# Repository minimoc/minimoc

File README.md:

# miniMoc

**Routeur MIDI hybride DAWless, fait main.**

🇬🇧 In English — miniMoc is a handmade, open-hardware DAWless MIDI router built around a Teensy 4.1: 5 MIDI inputs, 9 outputs, TRS TYPE A + USB Host, a 128x64 OLED screen and a rotary encoder. Route MIDI between your synths and machines with no computer. Its signature feature, Smart Mirror: plug in a PC and the miniMoc's physical ports reappear as identical virtual ports in your DAW — no setup, no drivers. Unplug and you're back to standalone mode. The project is at v0.5.2 (routing, Smart Mirror, MIDI clock sync, Flux transforms — transpose/harmonize/chord progressions —, MIDI generators — LFO/Euclidean/drum patterns — and SD presets are solid; continuous MIDI auto-recording to SD is postponed to a future version). Documentation is currently in French — English translation contributions are very welcome (see CONTRIBUTING.md). Licence: source-available, non-commercial (PolyForm NC for firmware, CC BY-NC for hardware) — personal use is free, commercial use requires permission.

Le miniMoc est un boîtier portable qui route le MIDI entre vos synthés, séquenceurs
et machines — sans ordinateur. cinq entrées (2 TRS Type A + 3 USB), neuf sorties (6 TRS TYPE A + 3 USB), USB Host, un écran OLED 128x64 pixels
et un encodeur pour tout piloter à la main.

> **Smart Mirror** — branchez un PC/MAC/LINUX/SMARTPHONE et les ports physiques du miniMoc réapparaissent
> à l'identique en ports virtuels dans votre DAW. Aucune configuration, aucun pilote
> à installer. Vous débranchez, vous repartez en mode autonome.

---

## Démonstrations vidéo

- **Le projet et l'appel aux compagnons** : https://www.youtube.com/watch?v=sc03914Uq1w
- **Présentation du hardware** (ce que vous recevez, comment c'est fait) : https://youtu.be/FKErdNdDdWI
- **La navigation dans les menus** : https://youtu.be/ahOwxcXlfOY
- **Le smartmirror expliqué** : https://youtu.be/d6lrl4uF-Bw

---

## État du projet — v0.5.2

Le miniMoc en est à sa version 0.5.2, assemblée à la main.

**Ce qui fonctionne et est éprouvé :**
- Routage MIDI complet (mode BASIC par matrice, mode FLUX avancé avec filtrage et
  remapping de canal)
- Smart Mirror (miroir des ports physiques vers le DAW)
- Synchronisation MIDI Clock (horloge interne réglable ou source externe) + écran TRANSPORT
- Transformateurs de Flux : transposition, harmonisation, réharmonisation sur une
  progression d'accords
- Générateurs MIDI internes : LFO, séquenceur euclidien, motifs de batterie pré-enregistrés
- Sauvegarde / rappel des configurations sur carte SD (32 presets utilisateur + 8 d'usine)
- Interface écran OLED + encodeur
- Mise à jour du firmware par OTA depuis l'éditeur web

**Reporté après la V1 :**
- Auto-enregistrement MIDI continu sur carte SD (capture automatique des jams). Le moteur
  existe dans le code mais reste désactivé par défaut : pas de commande pour démarrer/
  arrêter un enregistrement à la volée, pas de fermeture propre du fichier en cours
  d'usage. Sera retravaillé pour une version ultérieure — vos retours d'usage sur ce
  point précis restent les bienvenus.

---

## Ce que c'est (et ce que ce n'est pas)

Le miniMoc est un projet dans un esprit maker. Ce n'est pas un
produit fini sous coque fermée : il se présente sous forme de carte (PCB) avec son
Teensy 4.1, et un *bezel* maintient l'écran en position. Des premiers fichiers 3D de
boîtier et de socle existent (dossiers [`boitier/`](boitier/) et [`socle/`](socle/))
mais restent perfectibles — c'est un terrain de contribution ouvert pour qui aime la CAO.

---

## Matériel

- **Microcontrôleur** : Teensy 4.1 (PJRC)
- **Affichage** : écran OLED monochrome (I²C)
- **Entrées / sorties** : 2+3 IN MIDI, 6+3 OUT MIDI
- **Contrôle** : encodeur rotatif + bouton

Les fichiers de conception (schémas, PCB, BOM) se trouvent dans le dossier
[`hardware/`](hardware/). Le *bezel* à imprimer est dans [`bezel/`](bezel/).

---

## Firmware

Le code du firmware est dans [`firmware/`](firmware/). Il se compile avec
**l'IDE Arduino + Teensyduino**, pour Teensy 4.1.

### Dépendances

Ces bibliothèques **ne sont pas incluses dans ce dépôt**. Installez-les via le
gestionnaire de bibliothèques de l'IDE Arduino (ou elles sont fournies avec
Teensyduino) :

- U8g2
- Arduino MIDI Library (version 5+)
- USBHost_t36 *(fournie avec Teensyduino)*
- MTP_Teensy
- SdFat
- Encoder *(fournie avec Teensyduino)*
- Bounce2

> ⚠️ N'essayez pas de récupérer ces bibliothèques depuis ce dépôt : elles n'y sont
> volontairement pas. Passez par le gestionnaire de bibliothèques Arduino.

Les licences de ces dépendances sont détaillées dans
[`THIRD_PARTY_LICENSES.md`](THIRD_PARTY_LICENSES.md).

---

## Licence

**Sources ouvertes — usage personnel libre, commercialisation sur accord.**

- **Firmware** (dossier `firmware/`) : licence **PolyForm Noncommercial 1.0.0**.
  Vous pouvez l'utiliser, l'étudier, le modifier et le partager **pour un usage
  non commercial**.
- **Matériel** (dossiers `hardware/` et `bezel/`) : licence
  **Creative Commons Attribution-NonCommercial 4.0 (CC BY-NC 4.0)**.

Toute **utilisation commerciale** (vente, intégration dans un produit vendu, etc.)
nécessite mon accord préalable. Si vous souhaitez commercialiser quelque chose à
partir du miniMoc, contactez-moi : c'est tout à fait possible de s'entendre.

Voir les fichiers [`LICENSE`](LICENSE) (firmware) et
[`hardware/LICENSE`](hardware/LICENSE) (matériel).

---

## Contribuer

Le miniMoc avance avec celles et ceux qui l'utilisent. Retours d'usage,
corrections, idées de fonctionnalités, conception d'un boîtier complet : tout est
bienvenu. Voir [`CONTRIBUTING.md`](CONTRIBUTING.md).

---

*miniMoc — conçu et assemblé à la main par François Jacob.*

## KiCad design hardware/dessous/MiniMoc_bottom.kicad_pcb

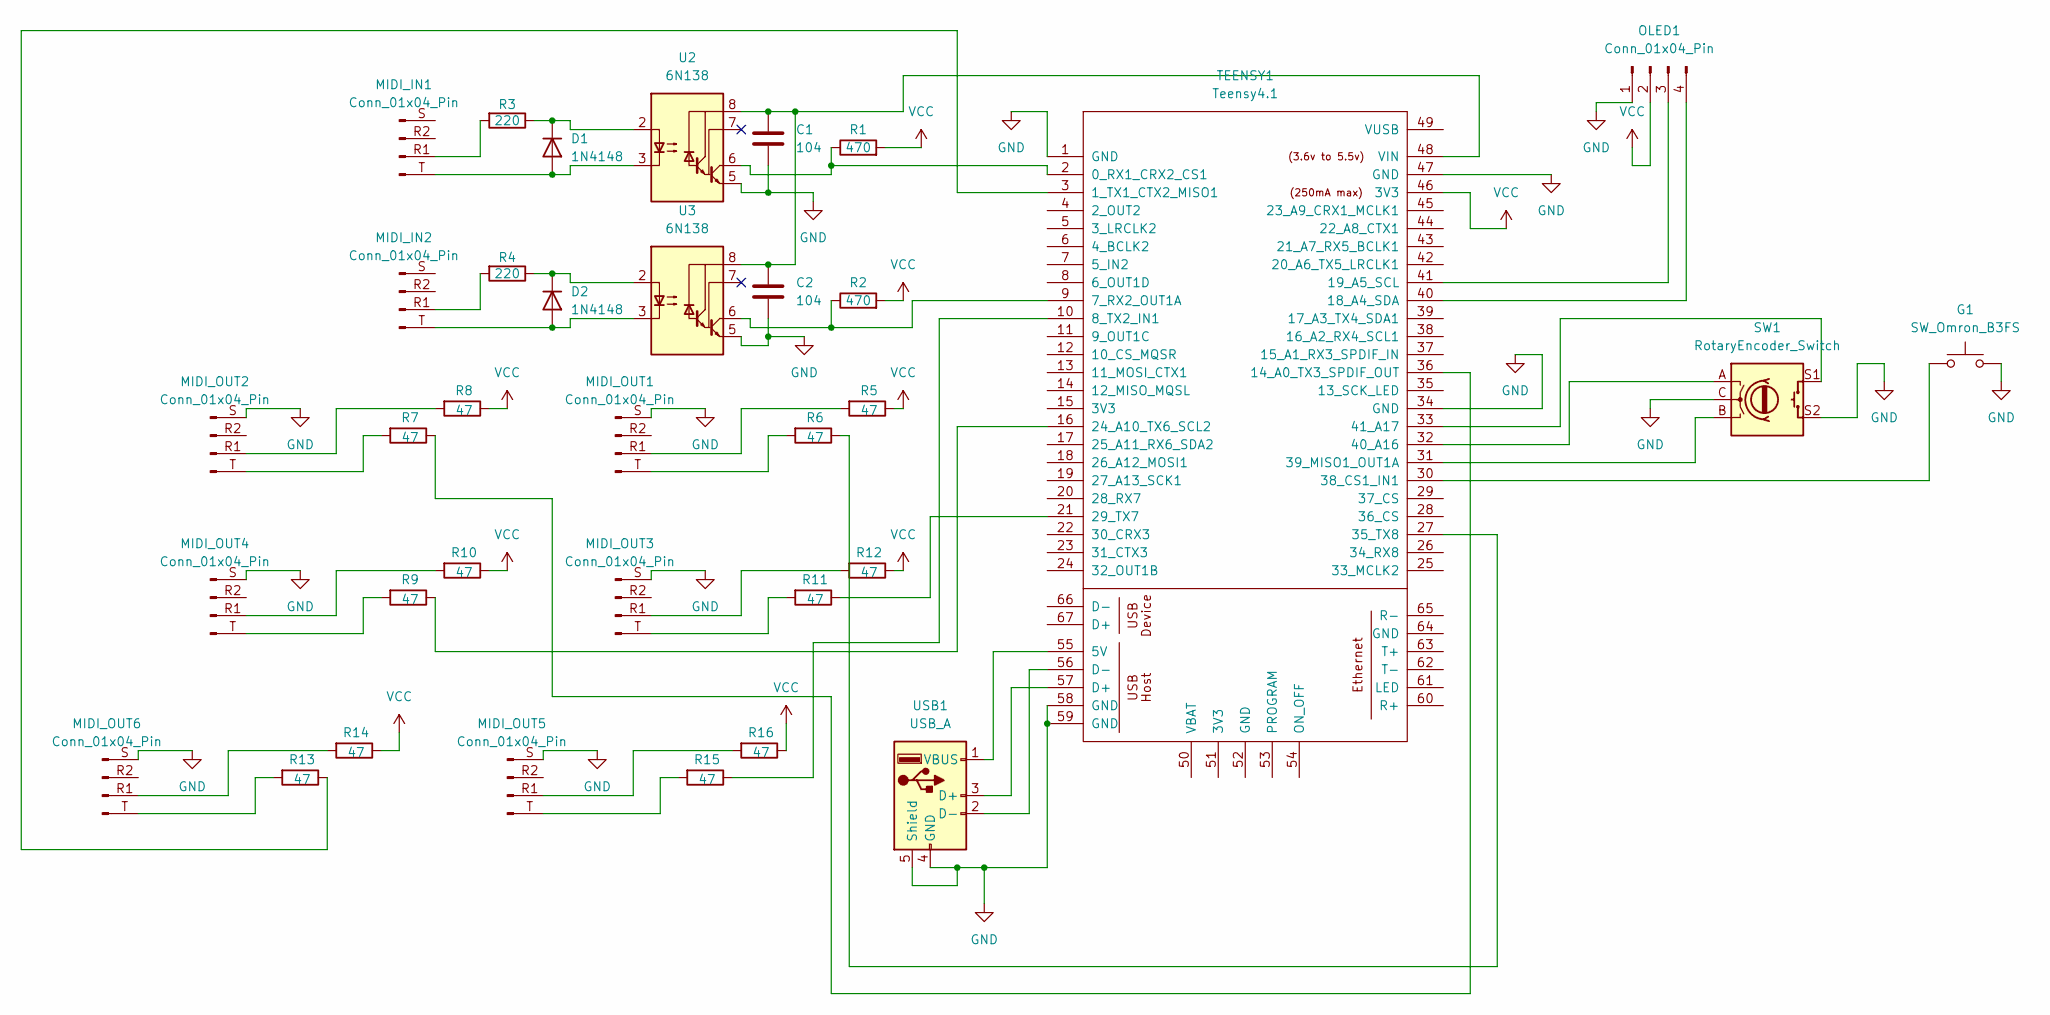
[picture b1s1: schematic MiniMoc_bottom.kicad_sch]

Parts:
C1, C2: 104; C_Disc_D5.0mm_W2.5mm_P2.50mm
D1, D2: 1N4148; D_DO-35_SOD27_P7.62mm_Horizontal
G1: SW_Omron_B3FS; SW_TH_Tactile_Omron_B3F-100x
MIDI_IN1, MIDI_IN2: Conn_01x04_Pin; Jack_3.5mm_PJ320E_Horizontal
MIDI_OUT1, MIDI_OUT2, MIDI_OUT3, MIDI_OUT4, MIDI_OUT5, MIDI_OUT6: Conn_01x04_Pin; Jack_3.5mm_PJ320E_Horizontal
OLED1: Conn_01x04_Pin; 128x64OLED
R1, R2: 470; R_Axial_DIN0207_L6.3mm_D2.5mm_P10.16mm_Horizontal
R3, R4: 220; R_Axial_DIN0207_L6.3mm_D2.5mm_P10.16mm_Horizontal
R5, R6, R7, R8, R9, R10, R11, R12, R13, R14, R15, R16: 47; R_Axial_DIN0207_L6.3mm_D2.5mm_P10.16mm_Horizontal
SW1: RotaryEncoder_Switch; RotaryEncoder_Alps_EC11E-Switch_Vertical_H20mm
TEENSY1: Teensy4.1; Teensy41
U2, U3: 6N138; DIP-8_W10.16mm_LongPads
USB1: USB_A; USB_A_Stewart_SS-52100-001_Horizontal

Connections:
GND: C1.2, C2.2, G1.2, MIDI_OUT1.S (Pin_1), MIDI_OUT2.S (Pin_1), MIDI_OUT3.S (Pin_1), MIDI_OUT4.S (Pin_1), MIDI_OUT5.S (Pin_1), MIDI_OUT6.S (Pin_1), OLED1.1, SW1.C, SW1.S2, TEENSY1.1 (GND), TEENSY1.34 (GND), TEENSY1.47 (GND), TEENSY1.58 (GND), TEENSY1.59 (GND), U2.5 (GND), U3.5 (GND), USB1.4 (GND), USB1.5 (Shield)
unnamed: D1.2 (A), MIDI_IN1.T (Pin_4), U2.3 (C2)
unnamed: D1.1 (K), R3.1, U2.2 (C1)
unnamed: D2.2 (A), MIDI_IN2.T (Pin_4), U3.3 (C2)
unnamed: D2.1 (K), R4.1, U3.2 (C1)
unnamed: MIDI_IN1.R1 (Pin_3), R3.2
unnamed: MIDI_IN2.R1 (Pin_3), R4.2
unnamed: MIDI_OUT1.R1 (Pin_3), R5.2
unnamed: MIDI_OUT1.T (Pin_4), R6.2
unnamed: MIDI_OUT2.R1 (Pin_3), R8.2
unnamed: MIDI_OUT2.T (Pin_4), R7.2
unnamed: MIDI_OUT3.R1 (Pin_3), R12.2
unnamed: MIDI_OUT3.T (Pin_4), R11.2
unnamed: MIDI_OUT4.R1 (Pin_3), R10.2
unnamed: MIDI_OUT4.T (Pin_4), R9.2
unnamed: MIDI_OUT5.R1 (Pin_3), R16.2
unnamed: MIDI_OUT5.T (Pin_4), R15.2
unnamed: MIDI_OUT6.R1 (Pin_3), R14.2
unnamed: MIDI_OUT6.T (Pin_4), R13.2
unnamed: OLED1.3, TEENSY1.41 (19_A5_SCL)
unnamed: OLED1.4, TEENSY1.40 (18_A4_SDA)
unnamed: R1.1, TEENSY1.2 (0_RX1_CRX2_CS1), U2.6 (VO2)
unnamed: R13.1, TEENSY1.3 (1_TX1_CTX2_MISO1)
unnamed: TEENSY1.55 (5V), USB1.1 (VBUS)
unnamed: R2.1, TEENSY1.9 (7_RX2_OUT1A), U3.6 (VO2)
unnamed: R15.1, TEENSY1.10 (8_TX2_IN1)
unnamed: R7.1, TEENSY1.36 (14_A0_TX3_SPDIF_OUT)
unnamed: R9.1, TEENSY1.16 (24_A10_TX6_SCL2)
unnamed: R11.1, TEENSY1.21 (29_TX7)
unnamed: R6.1, TEENSY1.27 (35_TX8)
unnamed: G1.1, TEENSY1.30 (38_CS1_IN1)
unnamed: SW1.B, TEENSY1.31 (39_MISO1_OUT1A)
unnamed: SW1.A, TEENSY1.32 (40_A16)
unnamed: SW1.S1, TEENSY1.33 (41_A17)
unnamed: C1.1, C2.1, TEENSY1.48 (VIN), U2.8 (VCC), U3.8 (VCC)
unnamed: TEENSY1.57 (D+), USB1.3 (D+)
unnamed: TEENSY1.56 (D-), USB1.2 (D-)
VCC: OLED1.2, R1.2, R2.2, R5.1, R8.1, R10.1, R12.1, R14.1, R16.1, TEENSY1.46 (3V3)

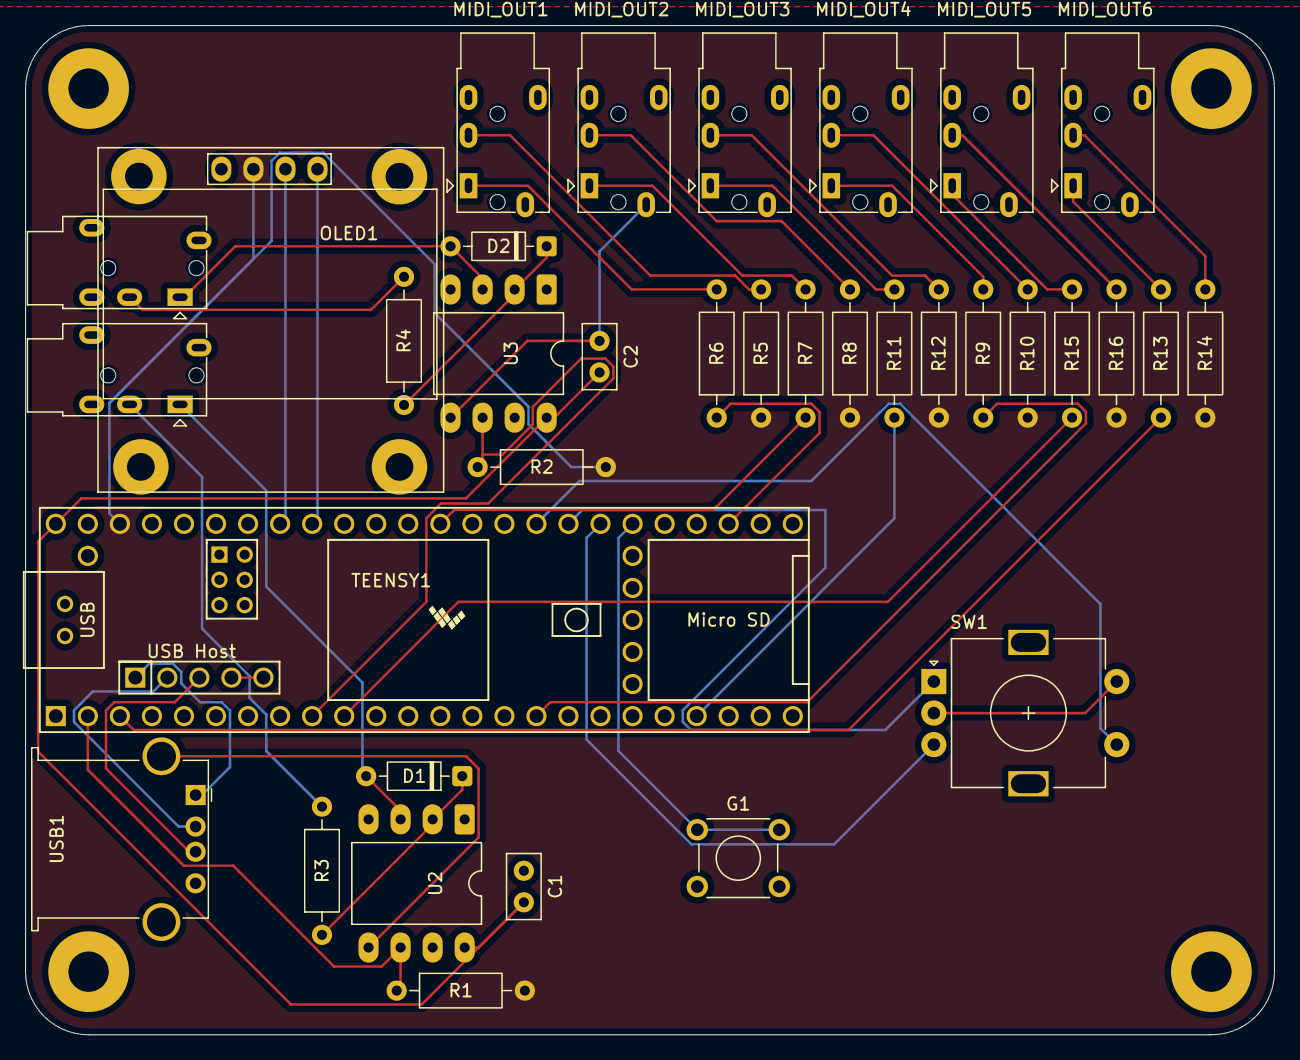
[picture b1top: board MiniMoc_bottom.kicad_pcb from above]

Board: 2 copper layers, 99.0 x 80.0 mm, 35 parts (0 on the bottom side), 38 nets.

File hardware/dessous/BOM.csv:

"Reference","Qty","Value","DNP","Exclude from BOM","Exclude from Board","Footprint","Datasheet"
"C1,C2","2","104","","","","Capacitor_THT:C_Disc_D5.0mm_W2.5mm_P2.50mm","~"
"D1,D2","2","1N4148","","","","Diode_THT:D_DO-35_SOD27_P7.62mm_Horizontal","https://assets.nexperia.com/documents/data-sheet/1N4148_1N4448.pdf"
"G1","1","SW_Omron_B3FS","","","","Button_Switch_THT:SW_TH_Tactile_Omron_B3F-100x","https://omronfs.omron.com/en_US/ecb/products/pdf/en-b3fs.pdf"
"MIDI_IN1,MIDI_IN2,MIDI_OUT1,MIDI_OUT2,MIDI_OUT3,MIDI_OUT4,MIDI_OUT5,MIDI_OUT6","8","Conn_01x04_Pin","","","","Connector_Audio:Jack_3.5mm_PJ320E_Horizontal","~"
"OLED1","1","Conn_01x04_Pin","","","","KICAD:128x64OLED","~"
"R1,R2","2","470","","","","Resistor_THT:R_Axial_DIN0207_L6.3mm_D2.5mm_P10.16mm_Horizontal","~"
"R3,R4","2","220","","","","Resistor_THT:R_Axial_DIN0207_L6.3mm_D2.5mm_P10.16mm_Horizontal","~"
"R5,R6,R7,R8,R9,R10,R11,R12,R13,R14,R15,R16","12","47","","","","Resistor_THT:R_Axial_DIN0207_L6.3mm_D2.5mm_P10.16mm_Horizontal","~"
"SW1","1","RotaryEncoder_Switch","","","","Rotary_Encoder:RotaryEncoder_Alps_EC11E-Switch_Vertical_H20mm","~"
"TEENSY1","1","Teensy4.1","","","","teensy:Teensy41",""
"U2,U3","2","6N138","","","","Package_DIP:DIP-8_W10.16mm_LongPads","http://www.onsemi.com/pub/Collateral/HCPL2731-D.pdf"
"USB1","1","USB_A","","","","Connector_USB:USB_A_Stewart_SS-52100-001_Horizontal","~"

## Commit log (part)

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2026-06-05 erreur dans le n° de version
2026-06-14 Sync display et online hex update
    - ajout de l'affichage du BPM reçu depuis le monitor
    - ajout dans le site web de la possibilité de choisir un .hex en ligne ou local
2026-06-16 sync smartmirror + weblink bug
